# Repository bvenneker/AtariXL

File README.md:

This Chat64 for Atari 800xl  (or 600xl with expanded memory)

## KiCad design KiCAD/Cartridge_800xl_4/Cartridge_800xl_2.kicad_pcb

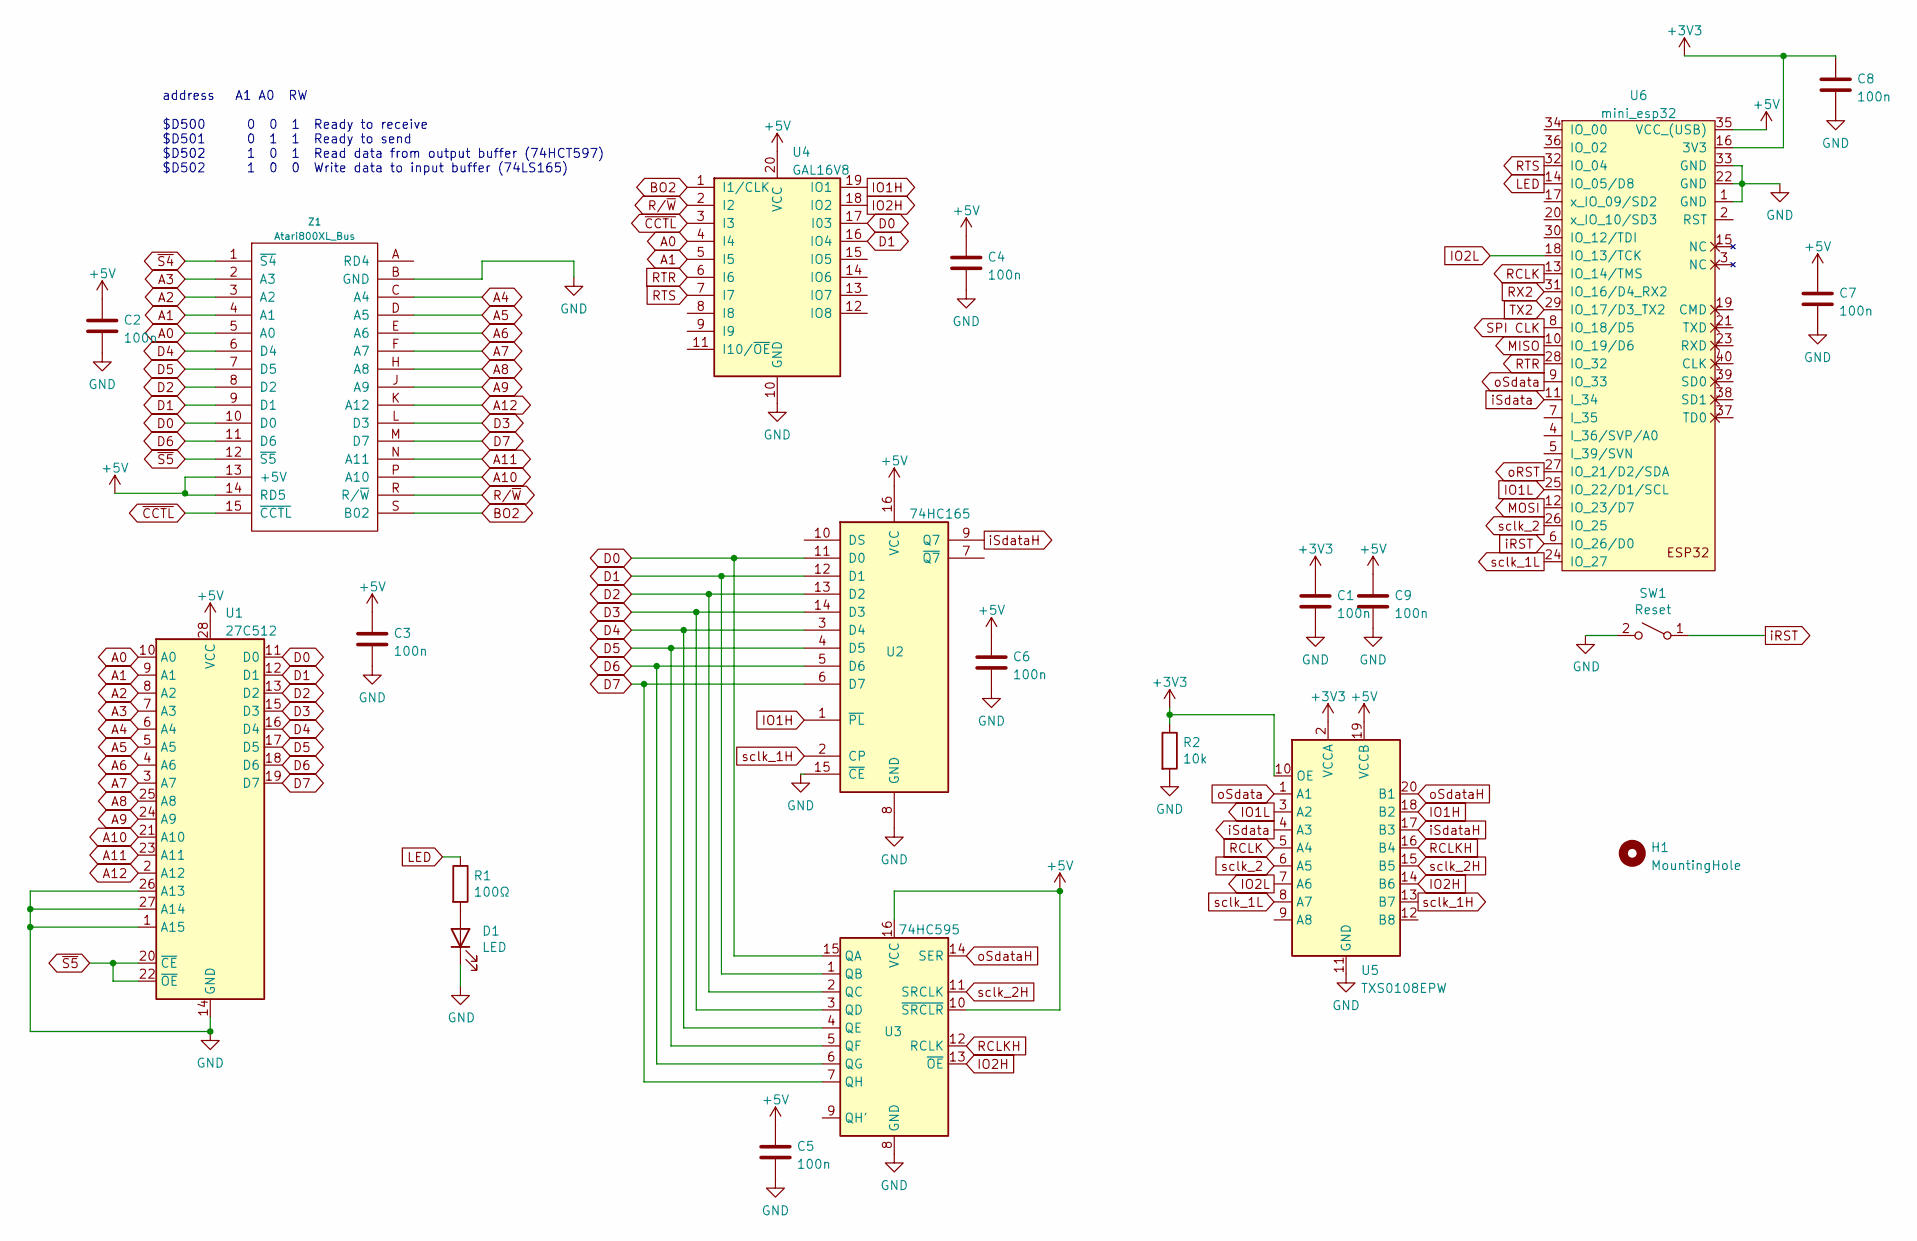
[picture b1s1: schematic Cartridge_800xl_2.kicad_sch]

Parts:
C1, C2, C3, C4, C5, C6, C7, C8, C9: 100n; C_0402_1005Metric
D1: LED; LED_0603_1608Metric
H1: MountingHole; MountingHole_3.2mm_M3
R1: 100Ω; R_0402_1005Metric
R2: 10k; R_0402_1005Metric
SW1: Reset; SW_PUSH_HALF_6mm
U1: 27C512; DIP-28_W15.24mm_LongPads
U2: 74HC165; SOIC-16_3.9x9.9mm_P1.27mm
U3: 74HC595; SOIC-16_3.9x9.9mm_P1.27mm
U4: GAL16V8; DIP-20_W7.62mm_LongPads
U5: TXS0108EPW; TSSOP-20_4.4x6.5mm_P0.65mm
U6: mini_esp32; ESP32_mini
Z1: Atari800XL_Bus; Atari_bus

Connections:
+3V3: C1.1, C8.1, R2.1, U5.2 (VCCA), U5.10 (OE), U6.16 (3V3)
+5V: C2.1, C3.1, C4.1, C5.1, C6.1, C7.1, C9.1, U1.28 (VCC), U2.16 (VCC), U3.10 (~SRCLR), U3.16 (VCC), U4.20 (VCC), U5.19 (VCCB), U6.35 (VCC_(USB)), Z1.13 (+5V), Z1.14 (RD5)
A0: U1.10 (A0), U4.4 (I4), Z1.5 (A0)
A1: U1.9 (A1), U4.5 (I5), Z1.4 (A1)
A2: U1.8 (A2), Z1.3 (A2)
A3: U1.7 (A3), Z1.2 (A3)
A4: U1.6 (A4), Z1.C (A4)
A5: U1.5 (A5), Z1.D (A5)
A6: U1.4 (A6), Z1.E (A6)
A7: U1.3 (A7), Z1.F (A7)
A8: U1.25 (A8), Z1.H (A8)
A9: U1.24 (A9), Z1.J (A9)
A10: U1.21 (A10), Z1.P (A10)
A11: U1.23 (A11), Z1.N (A11)
A12: U1.2 (A12), Z1.K (A12)
BO2: U4.1 (I1/CLK), Z1.S (B02)
D0: U1.11 (D0), U2.11 (D0), U3.15 (QA), U4.17 (I03), Z1.10 (D0)
D1: U1.12 (D1), U2.12 (D1), U3.1 (QB), U4.16 (IO4), Z1.9 (D1)
D2: U1.13 (D2), U2.13 (D2), U3.2 (QC), Z1.8 (D2)
D3: U1.15 (D3), U2.14 (D3), U3.3 (QD), Z1.L (D3)
D4: U1.16 (D4), U2.3 (D4), U3.4 (QE), Z1.6 (D4)
D5: U1.17 (D5), U2.4 (D5), U3.5 (QF), Z1.7 (D5)
D6: U1.18 (D6), U2.5 (D6), U3.6 (QG), Z1.11 (D6)
D7: U1.19 (D7), U2.6 (D7), U3.7 (QH), Z1.M (D7)
GND: C1.2, C2.2, C3.2, C4.2, C5.2, C6.2, C7.2, C8.2, C9.2, D1.1 (K), R2.2, SW1.2 (B), U1.1 (A15), U1.14 (GND), U1.26 (A13), U1.27 (A14), U2.8 (GND), U2.15 (~CE), U3.8 (GND), U4.10 (GND), U5.11 (GND), U6.1 (GND), U6.22 (GND), U6.33 (GND), Z1.B (GND)
IO1H: U2.1 (~PL), U4.19 (IO1), U5.18 (B2)
IO1L: U5.3 (A2), U6.25 (IO_22/D1/SCL)
IO2H: U3.13 (~OE), U4.18 (IO2), U5.14 (B6)
IO2L: U5.7 (A6), U6.18 (IO_13/TCK)
LED: R1.1, U6.14 (IO_05/D8)
MISO: U6.10 (IO_19/D6)
MOSI: U6.12 (IO_23/D7)
unnamed: D1.2 (A), R1.2
RCLK: U5.5 (A4), U6.13 (IO_14/TMS)
RCLKH: U3.12 (RCLK), U5.16 (B4)
RTR: U4.6 (I6), U6.28 (IO_32)
RTS: U4.7 (I7), U6.32 (IO_04)
RX2: U6.31 (IO_16/D4_RX2)
R/~W: U4.2 (I2), Z1.R (R/~W)
SPI CLK: U6.8 (IO_18/D5)
TX2: U6.29 (IO_17/D3_TX2)
iRST: SW1.1 (A), U6.6 (IO_26/D0)
iSdata: U5.4 (A3), U6.11 (I_34)
iSdataH: U2.9 (Q7), U5.17 (B3)
oRST: U6.27 (IO_21/D2/SDA)
oSdata: U5.1 (A1), U6.9 (IO_33)
oSdataH: U3.14 (SER), U5.20 (B1)
sclk_1H: U2.2 (CP), U5.13 (B7)
sclk_1L: U5.8 (A7), U6.24 (IO_27)
sclk_2: U5.6 (A5), U6.26 (IO_25)
sclk_2H: U3.11 (SRCLK), U5.15 (B5)
~CCTL: U4.3 (I3), Z1.15 (~CCTL)
~S4: Z1.1 (~S4)
~S5: U1.20 (~CE), U1.22 (~OE), Z1.12 (~S5)

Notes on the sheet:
address A1 A0 RW $D500 0 0 1 Ready to receive $D501 0 1 1 Ready to send $D502 1 0 1 Read data from output buffer (74HCT597) $D502 1 0 0 Write data to input buffer (74LS165)

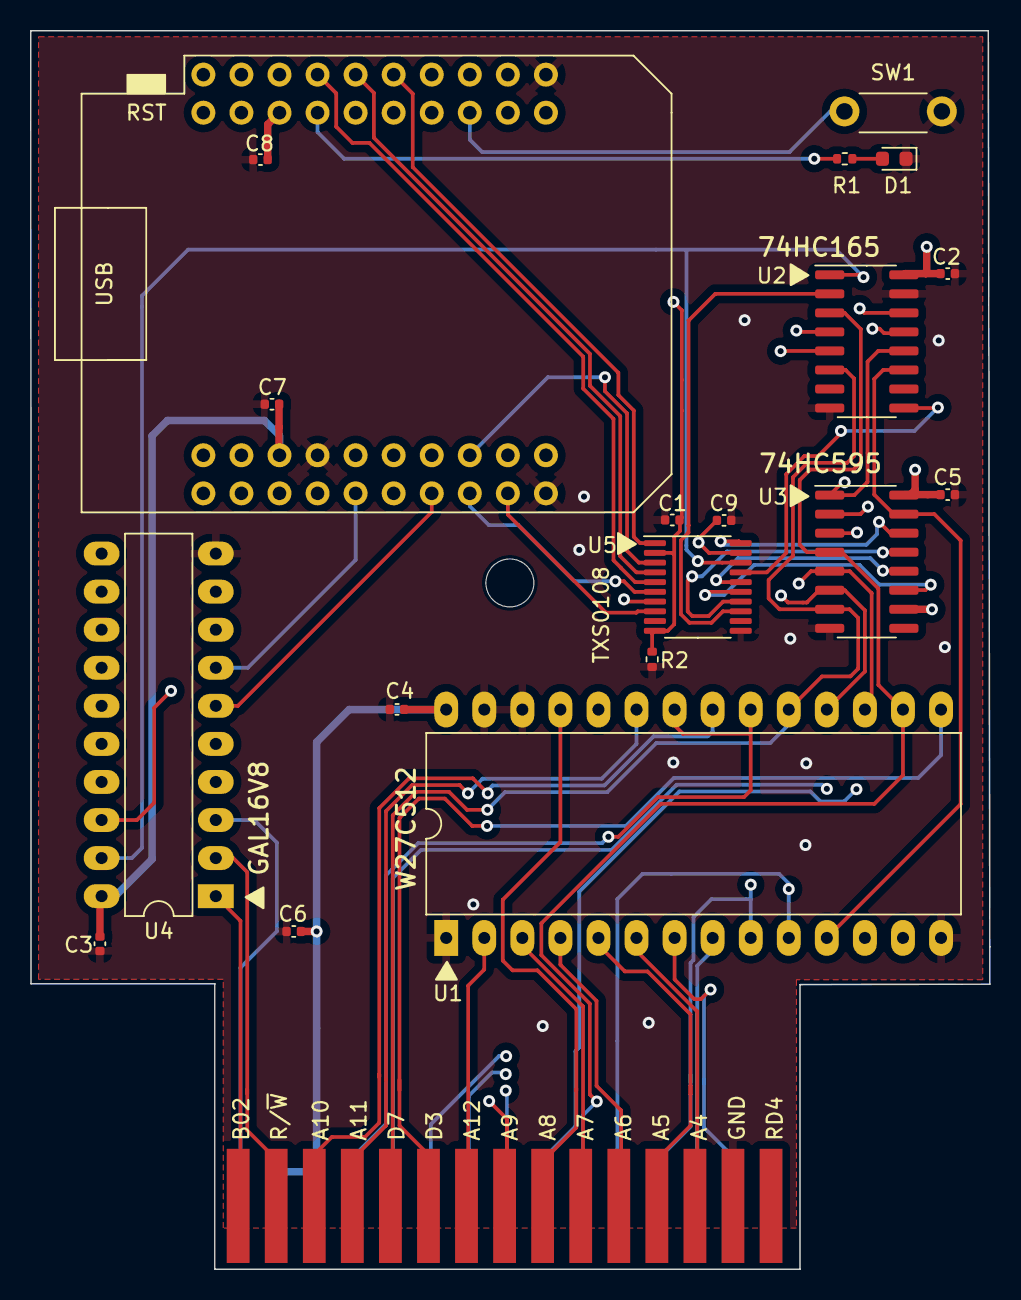
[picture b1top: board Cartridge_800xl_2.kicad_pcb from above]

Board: 4 copper layers, 64.0 x 82.6 mm, 21 parts (0 on the bottom side), 47 nets.

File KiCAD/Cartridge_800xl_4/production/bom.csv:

Designator,Footprint,Quantity,Value,LCSC Part #
"C1, C2, C3, C4, C5, C6, C7, C8, C9",0402,9,100n,
D1,0603,1,LED,
R1,0402,1,100Ω,
R2,0402,1,10k,
U2,SOIC-16_3.9x9.9mm_P1.27mm,1,74HC165,
U3,SOIC-16_3.9x9.9mm_P1.27mm,1,74HC595,
U5,TSSOP-20_4.4x6.5mm_P0.65mm,1,TXS0108EPW,

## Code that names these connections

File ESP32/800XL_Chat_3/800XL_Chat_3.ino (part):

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
#define CLED GPIO_NUM_5     // led on cartridge
#define sclk1 GPIO_NUM_27   // serial clock signal to the shift register
#define RCLK GPIO_NUM_14    // RCLK signal to the 165 shift register
#define sclk2 GPIO_NUM_25   // serial clock signal to the shift register
#define oSdata GPIO_NUM_33  // serial data to output buffer
#define RTR GPIO_NUM_32     // Ready to receive signal
#define RTS GPIO_NUM_4      // Ready to send signal


// ********************************
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

  // define outputs
  pinMode(RTR, OUTPUT);
  digitalWrite(RTR, LOW);
  pinMode(RTS, OUTPUT);
  digitalWrite(RTS, LOW);

  pinMode(oSdata, OUTPUT);
  pinMode(CLED, OUTPUT);
  digitalWrite(CLED, LOW);
  ready_to_receive(false);
  ready_to_send(false);
  pinMode(RCLK, OUTPUT);
  digitalWrite(RCLK, LOW);  // must be low
  pinMode(sclk1, OUTPUT);
  digitalWrite(sclk1, LOW);  // data shifts to serial data output on the transition from low to high.
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
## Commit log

2024-10-28 dev2
2024-10-30 building the code
2024-11-01 account_setup
2024-11-05 update pinout
2024-11-05 asmupdate
2024-11-05 start screen
2024-11-06 update backup and restore
2024-11-06 user list done
2024-11-07 nofade
2024-11-08 nothing
2024-11-08 update2
2024-11-13 more code
2024-11-15 wifi status
2024-11-26 bugje
2024-11-26 delete
2024-11-26 bugs
2024-11-29 more features
2024-11-30 colors!
2024-12-05 kicad updates
2024-12-06 debug user list issue
2024-12-08 version 3
    No more sub version in file name
    Fixed the userlist issue
2024-12-08 color
2024-12-08 bug fix
    you should not be able to submit an empty message
2024-12-10 timout in receive
    prevent an endless loop with a timeout
2024-12-17 comments
2024-12-18 fixed comments
2024-12-19 3.78 release
2024-12-20 kicad update
2024-12-27 send message fix
    very small bug when sending a private message from the public screen (whicg you should not do anyway):
    - pressing start to send the message worked fine
    - pressing shift return or control return worked fine
    - But pressing enter on the third line did not work.
    this is fixed now
2024-12-27 keep Attract at zero
2025-01-11 Fixed some bugs and added a blinking cursor
    Fixed some situations where the Atari would hang
    Added a blinking cursor (so you can also clearly see if it hangs)
2025-01-23 small update
    fixed a small bug with the blinking cursor
2025-01-31 small update
    sometimes, hearts would show up on the divider line.. that should be fixed now
2025-02-09 hearts
2025-03-05 pcb update
2025-05-24 servercode
2025-06-03 small update
    optimized setup procedure
2025-08-03 small changes
2025-09-01 working on scrolling
2025-09-03 Code optimalization
    I need to optimize the code to prepare for scrolling.
2025-10-16 working on Scrolling
    Scroll up starts to work (Controll + u)
2025-11-28 better splitbuffer
2025-11-28 fixed oopsie
2025-12-19 License Change
2025-12-19 Update license text
2025-12-23 Scrolling
2026-01-05 urlEncode fix
